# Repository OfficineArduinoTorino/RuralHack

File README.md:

# RuralHack

A place to store all the code and information for the RuralHack experimentations held during several workshops held **since summer 2016 in Italy and Mediterranean Areas** by the then-called Officine Arduino (now [Officine Innesto](http://officine.cc/)) and then called  [Ruralhub](https://www.facebook.com/RuralHub), now migrated itself in [Ruralhack](http://www.ruralhack.org/).

Ruralhack is now purchasable for Italian Public Administration through [MEPA](https://www.acquistinretepa.it/)

# Structure of the Repository

You can see two main folders.
In the **[/exercises](https://github.com/OfficineArduinoTorino/RuralHack/tree/master/exercises)** you can find basic examples of use of several sensors used in the workshop, while in the **[/libraries](https://github.com/OfficineArduinoTorino/RuralHack/tree/master/libraries)** folder some of the main libraries used are hosted. Unfortunately some of them have a intense development so we strongly advice you to download them - where possible - from the **Arduino Library Manager** if using **Arduino Java IDE**.

# The Kit

The list of components used in the workshop is a kit on sale on the [Arduino Store](https://store.arduino.cc/rural-hack-kit).

The Kit (designed to be used with a [Arduino MKR board](https://store.arduino.cc/arduino-genuino/arduino-genuino-mkr-family)), while most of the code you'll find here is tested on [Arduino MKR 1000](https://store.arduino.cc/arduino-mkr1000-with-headers-mounted) and [Arduino MKR 1010](https://store.arduino.cc/arduino-mkr-wifi-1010) features:

- Humidity Sensor (DHT22)
- Log-scale Analog Light Sensor ([Ga1a12s202 in its Adafruit's Flavour](https://www.adafruit.com/product/1384))
- [Soil Moisture Sensor](https://www.tindie.com/products/miceuz/i2c-soil-moisture-sensor) (aka the slim chirp) from [Miceuz](https://www.tindie.com/stores/miceuz/)
- [Grove Relay Module](http://seeedstudio.com/depot/Grove-Relay-p-769.html) from Seeed
- Resistors / pushbuttons / connectors

# The workshop

We've done this workshop several times in the last two years.

The main aim of a this workshop is giving people access to new technologies. We have released all the teaching material for you to toy around the kit *indipendently*.

Most codes are not by us, in some cases adaptations of somebodyelse's code and projects, we tried to create diagrams of some specific setups using [Fritzing](fritzing.org/). Most of the Workshop notes are in the /presentation-materials folder

The basic idea behind the workshop was create some sort of automatization inside of a rural scenario, with wifi connectivity and not a large area to look after. We started little to grow big.

## 1st RuralHack Workshop back in 2016

## Ruralhack @ Calvanico 2018

## Muse Workshop 2018

([Watch the entire Flickr Ambum of the first  RuralHack](https://www.flickr.com/photos/142132017@N03/albums/72157670025633602) by [Ruralhub](ruralhub.it/en/)) or [the latest one of November 2018 at Muse Museum of Trento, Italy](https://www.flickr.com/photos/musefablab/sets/72157702272359111/)

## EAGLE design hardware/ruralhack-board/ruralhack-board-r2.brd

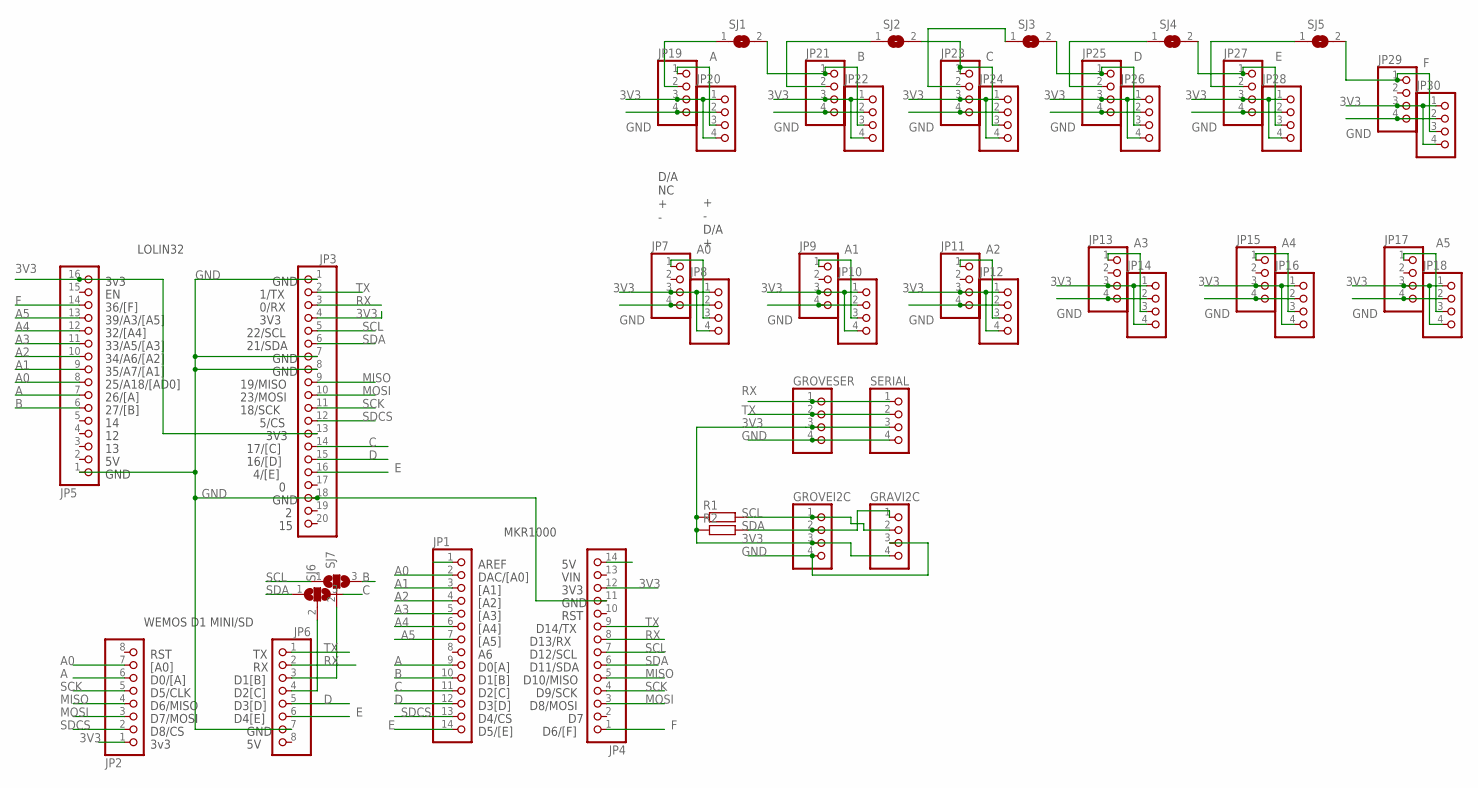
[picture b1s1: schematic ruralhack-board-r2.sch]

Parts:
GRAVI2C: PINHD-1X4; 1X04
GROVEI2C: PINHD-1X4; 1X04
GROVESER: PINHD-1X4; 1X04
JP1, JP4: PINHD-1X14; 1X14
JP2, JP6: PINHD-1X8; 1X08
JP3: PINHD-1X20; 1X20
JP5: PINHD-1X16; 1X16
JP7, JP8, JP9, JP10, JP11, JP12, JP13, JP14, JP15, JP16, JP17, JP18, JP19, JP20, JP21, JP22, JP23, JP24, JP25, JP26, JP27, JP28, JP29, JP30: PINHD-1X4; 1X04
R1, R2: R-EU_0204/7; 0204/7
SERIAL: PINHD-1X4; 1X04
SJ1, SJ2, SJ3, SJ4, SJ5: SJW
SJ6, SJ7: SJ2WW; SJ_2W

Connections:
3V3: GRAVI2C.4, GROVEI2C.3, GROVESER.3, JP2.1, JP3.4, JP3.13, JP4.12, JP5.16, JP7.3, JP8.1, JP8.4, JP9.3, JP10.1, JP10.4, JP11.3, JP12.1, JP12.4, JP13.3, JP14.1, JP14.4, JP15.3, JP16.1, JP16.4, JP17.3, JP18.1, JP18.4, JP19.3, JP20.1, JP20.4, JP21.3, JP22.1, JP22.4, JP23.3, JP24.1, JP24.4, JP25.3, JP26.1, JP26.4, JP27.3, JP28.1, JP28.4, JP29.3, JP30.1, JP30.4, R1.1, R2.1, SERIAL.3
A: JP1.9, JP2.6, JP5.7, JP19.1, JP20.3
A0: JP1.2, JP2.7, JP5.8, JP7.1, JP8.3
A1: JP1.3, JP5.9, JP9.1, JP10.3
A2: JP1.4, JP5.10, JP11.1, JP12.3
A3: JP1.5, JP5.11, JP13.1, JP14.3
A4: JP1.6, JP5.12, JP15.1, JP16.3
A5: JP1.7, JP5.13, JP17.1, JP18.3
B: JP1.10, JP5.6, JP21.1, JP22.3, SJ1.2, SJ7.3
C: JP1.11, JP3.14, JP23.1, JP24.3, SJ2.2, SJ6.3
D: JP1.12, JP3.15, JP6.5, JP25.1, JP26.3, SJ3.2
E: JP1.14, JP3.16, JP6.6, JP27.1, JP28.3, SJ4.2
F: JP4.1, JP5.14, JP29.1, JP30.3, SJ5.2
GND: GRAVI2C.3, GROVEI2C.4, GROVESER.4, JP3.1, JP3.7, JP3.8, JP3.18, JP4.11, JP5.1, JP6.7, JP7.4, JP8.2, JP9.4, JP10.2, JP11.4, JP12.2, JP13.4, JP14.2, JP15.4, JP16.2, JP17.4, JP18.2, JP19.4, JP20.2, JP21.4, JP22.2, JP23.4, JP24.2, JP25.4, JP26.2, JP27.4, JP28.2, JP29.4, JP30.2, SERIAL.4
MISO: JP2.4, JP3.9, JP4.5
MOSI: JP2.3, JP3.10, JP4.3
unnamed: JP19.2, SJ1.1
unnamed: JP21.2, SJ2.1
unnamed: JP23.2, SJ3.1
unnamed: JP25.2, SJ4.1
unnamed: JP6.3, SJ7.2
unnamed: JP27.2, SJ5.1
unnamed: JP6.4, SJ6.2
RX: GROVESER.1, JP3.3, JP4.8, JP6.2, SERIAL.1
SCK: JP2.5, JP3.11, JP4.4
SCL: GRAVI2C.2, GROVEI2C.1, JP3.5, JP4.7, R1.2, SJ7.1
SDA: GRAVI2C.1, GROVEI2C.2, JP3.6, JP4.6, R2.2, SJ6.1
SDCS: JP1.13, JP2.2, JP3.12
TX: GROVESER.2, JP3.2, JP4.9, JP6.1, SERIAL.2

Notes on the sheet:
3v3
D8/CS
D7/MOSI
D6/MISO
D5/CLK
D0/[A]
[A0]
RST
GND
D4[E]
D3[D]
D2[C]
D1[B]
WEMOS D1 MINI/SD
MKR1000
AREF
DAC/[A0]
[A1]
[A2]
[A3]
[A4]
[A5]
D0[A]
D4/CS
D5/[E]
D6/[F]
D8/MOSI
D9/SCK
D10/MISO
D11/SDA
D12/SCL
D13/RX
D14/TX
3V3
VIN
LOLIN32
36/[F]
39/A3/[A5]
32/[A4]
33/A5/[A3]

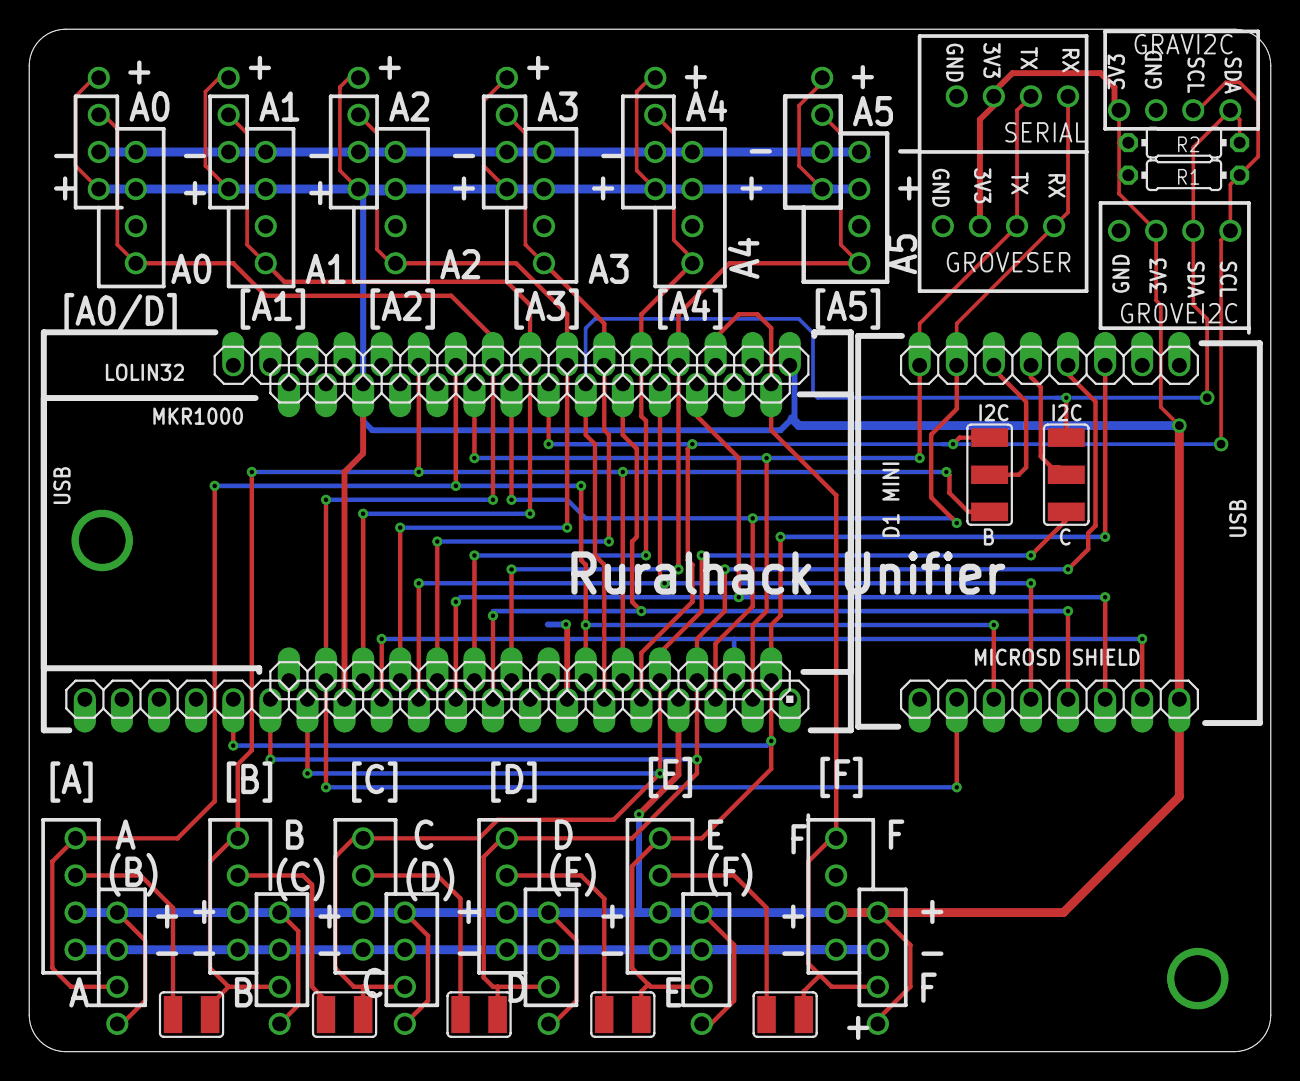
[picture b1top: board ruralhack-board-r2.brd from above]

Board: 2 copper layers, 85.0 x 70.0 mm, 43 parts (0 on the bottom side), 29 nets.

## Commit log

2016-06-24 The Arduino code for the Sensor (please disregard the DTMF stuff, it uses Serial) and the Receiver (MKR1000)
2016-06-24 Added some beeping functionlaity, the higher the beep the more moist...
2016-06-24 some thoughts
2016-06-29 fixed library
2016-07-02 added all examples
2016-07-02 added gitignore
2016-07-02 apiKeys as variable
2016-07-02 made apikey a var
2016-07-02 added parsing temperature
2016-07-26 some more documentation
2016-07-26 final
2016-07-26 finalq
2016-07-26 adding some pics
2016-07-26 adding some final things
2018-03-20 Unifier board initial commit
2018-06-04 updating pdf
2018-06-05 Add selection solder jumper for i2c or gpio operation on D1 mini
2018-11-28 Major Update after Muse Workshop
2018-11-28 updating images
2019-07-20 aggiunta foto
2019-07-20 aggiuntu documentazione quaderno di campagna
